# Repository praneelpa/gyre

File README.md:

<h1 align="center">
  <br>
  
  <br>
  Gyre V1
  <br>
</h1>

<h4 align="center">
  An ESP32-S3 development board with a live 3D orientation view and voice control for LED strips!
</h4>

> **🚧 Work in progress:** Gyre is in the design stage. The PCB routing has been completed, but nothing has been built or tested yet.

## Features

- **ESP32-S3-MINI-1** module with WiFi, Bluetooth and native USB
- **Live 3D view** - a 6-axis IMU drives a web page that rotates a 3D model of the board in real time, over USB
- **Voice control** - an I2S microphone (ICS-43434) and a small on-device model that listens for commands and controls an external NeoPixel LED strip
- **Raspberry Pi Pico form factor** (21 x 51 mm) with Pico-style 2.54 mm pin headers
- **Still a normal ESP32** - every usable GPIO goes to the headers, so blinking an LED or flashing your own firmware works as usual. Anything onboard that uses a pin has a solder jumper, so you can free the pin
- **USB-C** for power, programming and data
- **BOOT and RESET buttons**
- **Three status LEDs** - PWR, USR (for your own code) and ACT (blinks on activity)
- **4-layer PCB** with a black solder mask and gold (ENIG) pads

## Functionality

### Live 3D view

1. The IMU measures the board's motion.
2. The ESP32 combines the readings into an orientation and sends it over USB serial.
3. A web page in Chrome or Edge reads the serial port (Web Serial) and rotates a 3D model of the board to match.

There's no driver or app to install. The IMU has no compass, so left-right turning (yaw) will slowly drift. That's a known limit of this kind of sensor.

### Voice control

1. The microphone sends audio to the ESP32 over I2S.
2. A small model running on the ESP32 listens for trained words such as "on", "off", colors and brightness levels.
3. Recognized words are combined into a command, for example "blue lights".
4. The ESP32 sends the command to the LED strip through a level shifter on the data line.

The strip is a separate part and has its own 5 V supply. Gyre only sends the data signal, because a room-sized strip can draw far more current than USB provides. The model is trained on a fixed set of words, so it works best for the voice it was trained on.

## PCB

Designed in KiCad. The board uses a 4-layer stackup (SIG/GND/PWR/SIG) with a black solder mask, gold (ENIG) pads and white silkscreen.

### Schematic

### PCB Layers

**Layer 1 (F.Cu):**

**Layer 2 (Ground):**

**Layer 3 (+3.3V):**

**Layer 4 (B.Cu):**

**Front View:**

**Back View:**

### BOM
| Designator            | Footprint                         | Qty Per Board | Order Qty | Value              | Price   | LCSC Part Number | LCSC Part Link                                     |
|-----------------------|-----------------------------------|---------------|-----------|--------------------|---------|------------------|----------------------------------------------------|
| C1                    | 0805                              | 1             | 20        | 10u                | $0.4220 | C1713            | https://www.lcsc.com/product-detail/C1713.html     |
| C10, C11, C12, C4, C7 | 0805                              | 5             | 20        | 0.1u               | $0.2780 | C49678           | https://www.lcsc.com/product-detail/C49678.html    |
| C3                    | 0805                              | 1             | 20        | 1u                 | $0.5240 | C24123           | https://www.lcsc.com/product-detail/C24123.html    |
| C5                    | 0805                              | 1             | 10        | 22u                | $0.2190 | C29277           | https://www.lcsc.com/product-detail/C29277.html    |
| C8                    | 0805                              | 1             | 100       | 10n                | $0.6600 | C282728          | https://www.lcsc.com/product-detail/C282728.html   |
| C9                    | 0805                              | 1             | 20        | 2.2u               | $0.9680 | C1731            | https://www.lcsc.com/product-detail/C1731.html     |
| D1                    | SOT-23-6_L2.9-W1.6-P0.95-LS2.8-BL | 1             | 5         | USBLC6-2SC6        | $0.7680 | C7519            | https://www.lcsc.com/product-detail/C7519.html     |
| D2                    | 0805                              | 1             | 50        | ACT red            | $0.6300 | C84256           | https://www.lcsc.com/product-detail/C84256.html    |
| D3                    | 0805                              | 1             | 100       | USR blue           | $0.5900 | C7496833         | https://www.lcsc.com/product-detail/C7496833.html  |
| D4                    | 0805                              | 1             | 50        | VOICE white        | $0.4150 | C55072219        | https://www.lcsc.com/product-detail/C55072219.html |
| J1, J2, J3, J4        | PinHeaders_1x40_P2.54mm_Vertical  | 2             | 5         | Conn_01x40         | $0.8160 | C2337            | https://www.lcsc.com/product-detail/C2337.html     |
| R1, R2                | 0805                              | 2             | 100       | 5.1K               | $0.2900 | C27834           | https://www.lcsc.com/product-detail/C27834.html    |
| R10, R11              | 0805                              | 2             | 100       | 100                | $0.3500 | C105577          | https://www.lcsc.com/product-detail/C105577.html   |
| R3, R6, R8            | 0805                              | 3             | 100       | 10k                | $0.3200 | C17414           | https://www.lcsc.com/product-detail/C17414.html    |
| R4                    | 0805                              | 1             | 100       | 499                | $0.2300 | C2933453         | https://www.lcsc.com/product-detail/C2933453.html  |
| R5                    | 0805                              | 1             | 100       | 100k               | $0.3600 | C149504          | https://www.lcsc.com/product-detail/C149504.html   |
| R7, R9                | 0805                              | 2             | 100       | 330                | $0.2500 | C2930157         | https://www.lcsc.com/product-detail/C2930157.html  |
| SW1                   | SW-SMD_L3.9-W2.9-LS4.8            | 1             | 5         | BOOT               | $0.4295 | C596279          | https://www.lcsc.com/product-detail/C596279.html   |
| SW2                   | SW-SMD_L3.9-W2.9-LS4.8            | 1             | 5         | RESET              | $0.4295 | C596279          | https://www.lcsc.com/product-detail/C596279.html   |
| U1                    | SOT-25-5_L2.9-W1.6-P0.95-LS2.8-BL | 1             | 5         | AP2112K-3.3TRG1    | $0.8415 | C51118           | https://www.lcsc.com/product-detail/C51118.html    |
| U2                    | BULETM-SMD_ESP32-S3-MINI-1-N8     | 1             | 1         | ESP32-S3-MINI-1-N8 | $4.7617 | C2913206         | https://www.lcsc.com/product-detail/C2913206.html  |
| U3                    | LGA-14_L3.0-W2.5-P0.50-TL         | 1             | 2         | ICM-42688-P        | $3.6600 | C54308212        | https://www.lcsc.com/product-detail/C54308212.html |
| U4                    | MIC-SMD_6P-L3.5-W2.7-P0.90-BL     | 1             | 1         | ICS-43434_C5656610 | $4.2908 | C5656610         | https://www.lcsc.com/product-detail/C5656610.html  |
| U5                    | SOT-25-5_L2.9-W1.6-P0.95-LS2.8-BL | 1             | 1         | 74AHCT1G125GV      | $0.0734 | C52140417        | https://www.lcsc.com/product-detail/C52140417.html |
| USB1                  | USB-C-SMD_TYPE-C-16PIN-2MD-073    | 1             | 20        | TYPE-C 16PIN 2MD   | $1.3900 | C2765186         | https://www.lcsc.com/product-detail/C2765186.html  |

## Credits

This project uses:

- [KiCad](https://www.kicad.org/)
- [Espressif](https://www.espressif.com/) for the ESP32-S3 module and its hardware design guidelines

---

> GitHub [@praneelpa](https://github.com/praneelpa) ·
> MIT License

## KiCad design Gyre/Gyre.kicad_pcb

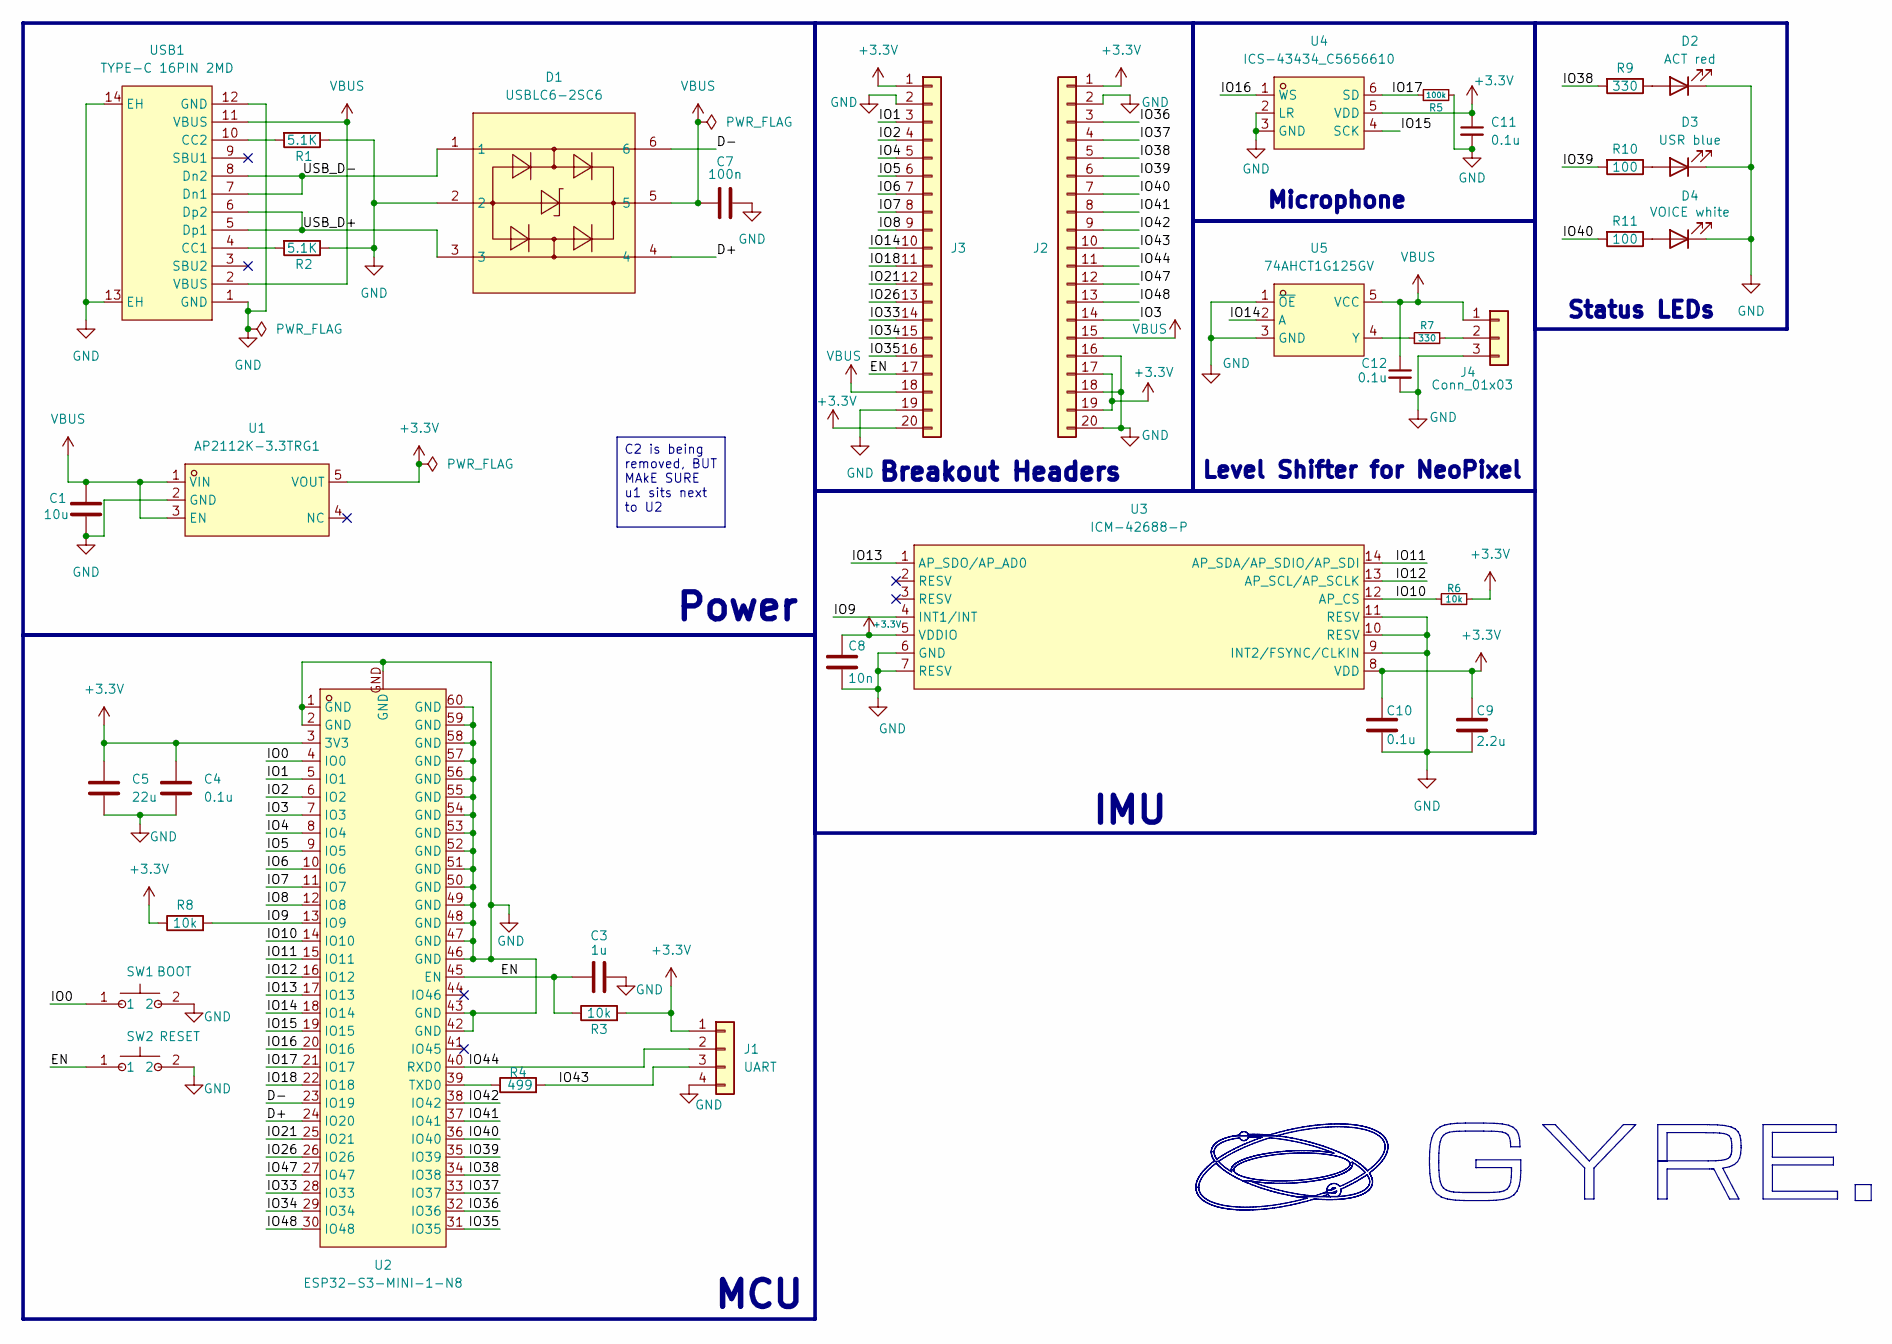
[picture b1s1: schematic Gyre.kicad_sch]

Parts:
C1: 10u; C_0805_2012Metric_Pad1.18x1.45mm_HandSolder
C3: 1u; C_0805_2012Metric_Pad1.18x1.45mm_HandSolder
C4, C10, C11, C12: 0.1u; C_0805_2012Metric_Pad1.18x1.45mm_HandSolder
C5: 22u; C_0805_2012Metric_Pad1.18x1.45mm_HandSolder
C7: 100n; C_0805_2012Metric_Pad1.18x1.45mm_HandSolder
C8: 10n; C_0805_2012Metric_Pad1.18x1.45mm_HandSolder
C9: 2.2u; C_0805_2012Metric_Pad1.18x1.45mm_HandSolder
D1: USBLC6-2SC6; SOT-23-6_L2.9-W1.6-P0.95-LS2.8-BL; MPN USBLC6-2SC6; LCSC Part C7519
D2: ACT red; LED_0805_2012Metric_Pad1.15x1.40mm_HandSolder
D3: USR blue; LED_0805_2012Metric_Pad1.15x1.40mm_HandSolder
D4: VOICE white; LED_0805_2012Metric_Pad1.15x1.40mm_HandSolder
J1: UART; PinHeader_1x04_P2.54mm_Vertical
J2, J3: Conn_01x20; PinHeader_1x20_P2.54mm_Vertical
J4: Conn_01x03; PinHeader_1x03_P2.54mm_Vertical
R1, R2: 5.1K; R_0805_2012Metric_Pad1.20x1.40mm_HandSolder
R3, R6, R8: 10k; R_0805_2012Metric_Pad1.20x1.40mm_HandSolder
R4: 499; R_0805_2012Metric_Pad1.20x1.40mm_HandSolder
R5: 100k; R_0805_2012Metric_Pad1.20x1.40mm_HandSolder
R7, R9: 330; R_0805_2012Metric_Pad1.20x1.40mm_HandSolder
R10, R11: 100; R_0805_2012Metric_Pad1.20x1.40mm_HandSolder
SW1: BOOT; SW-SMD_L3.9-W2.9-LS4.8; MPN TS-1807R-2026; LCSC Part C596279
SW2: RESET; SW-SMD_L3.9-W2.9-LS4.8; MPN TS-1807R-2026; LCSC Part C596279
U1: AP2112K-3.3TRG1; SOT-25-5_L2.9-W1.6-P0.95-LS2.8-BL; MPN AP2112K-3.3TRG1; LCSC Part C51118
U2: ESP32-S3-MINI-1-N8; BULETM-SMD_ESP32-S3-MINI-1-N8; MPN ESP32-S3-MINI-1-N8; LCSC Part C2913206
U3: ICM-42688-P; LGA-14_L3.0-W2.5-P0.50-TL; MPN ICM-42688-P; LCSC Part C1850418
U4: ICS-43434_C5656610; MIC-SMD_6P-L3.5-W2.7-P0.90-BL; MPN ICS-43434; LCSC Part C5656610
U5: 74AHCT1G125GV; SOT-25-5_L2.9-W1.6-P0.95-LS2.8-BL; MPN 74AHCT1G125GV; LCSC Part C52140417
USB1: TYPE-C 16PIN 2MD; USB-C-SMD_TYPE-C-16PIN-2MD-073; MPN TYPE-C 16PIN 2MD(073); LCSC Part C2765186

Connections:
+3.3V: C4.1, C5.1, C8.1, C9.1, C10.1, C11.1, J1.1, J2.1, J2.17, J2.19, J3.1, J3.20, R3.2, R6.2, R8.1, U1.5 (VOUT), U2.3 (3V3), U3.5 (VDDIO), U3.8 (VDD), U4.5 (VDD)
/D+: D1.4, U2.24 (IO20)
/D-: D1.6, U2.23 (IO19)
/EN: C3.1, J3.17, R3.1, SW2.1, U2.45 (EN)
/IO0: SW1.1, U2.4 (IO0)
/IO1: J3.3, U2.5 (IO1)
/IO2: J3.4, U2.6 (IO2)
/IO3: J2.14, U2.7 (IO3)
/IO4: J3.5, U2.8 (IO4)
/IO5: J3.6, U2.9 (IO5)
/IO6: J3.7, U2.10 (IO6)
/IO7: J3.8, U2.11 (IO7)
/IO8: J3.9, U2.12 (IO8)
/IO9: R8.2, U2.13 (IO9), U3.4 (INT1/INT)
/IO10: R6.1, U2.14 (IO10), U3.12 (AP_CS)
/IO11: U2.15 (IO11), U3.14 (AP_SDA/AP_SDIO/AP_SDI)
/IO12: U2.16 (IO12), U3.13 (AP_SCL/AP_SCLK)
/IO13: U2.17 (IO13), U3.1 (AP_SDO/AP_AD0)
/IO14: J3.10, U2.18 (IO14), U5.2 (A)
/IO15: U2.19 (IO15), U4.4 (SCK)
/IO16: U2.20 (IO16), U4.1 (WS)
/IO17: R5.1, U2.21 (IO17), U4.6 (SD)
/IO18: J3.11, U2.22 (IO18)
/IO21: J3.12, U2.25 (IO21)
/IO26: J3.13, U2.26 (IO26)
/IO33: J3.14, U2.28 (IO33)
/IO34: J3.15, U2.29 (IO34)
/IO35: J3.16, U2.31 (IO35)
/IO36: J2.3, U2.32 (IO36)
/IO37: J2.4, U2.33 (IO37)
/IO38: J2.5, R9.2, U2.34 (IO38)
/IO39: J2.6, R10.2, U2.35 (IO39)
/IO40: J2.7, R11.2, U2.36 (IO40)
/IO41: J2.8, U2.37 (IO41)
/IO42: J2.9, U2.38 (IO42)
/IO43: J1.3, J2.10, R4.2
/IO44: J1.2, J2.11, U2.40 (RXD0)
/IO47: J2.12, U2.27 (IO47)
/IO48: J2.13, U2.30 (IO48)
/USB_D+: D1.3, USB1.5 (Dp1), USB1.6 (Dp2)
/USB_D-: D1.1, USB1.7 (Dn1), USB1.8 (Dn2)
GND: C1.2, C3.2, C4.2, C5.2, C7.2, C8.2, C9.2, C10.2, C11.2, C12.2, D1.2, D2.1 (K), D3.1 (K), D4.1 (K), J1.4, J2.2, J2.16, J2.18, J2.20, J3.2, J3.19, J4.3, R1.1, R2.1, R5.2, SW1.2, SW2.2, U1.2 (GND), U2.1 (GND), U2.2 (GND), U2.42 (GND), U2.43 (GND), U2.46 (GND), U2.47 (GND), U2.48 (GND), U2.49 (GND), U2.50 (GND), U2.51 (GND), U2.52 (GND), U2.53 (GND), U2.54 (GND), U2.55 (GND), U2.56 (GND), U2.57 (GND), U2.58 (GND), U2.59 (GND), U2.60 (GND), U2.GND, U3.6 (GND), U3.7 (RESV), U3.9 (INT2/FSYNC/CLKIN), U3.10 (RESV), U3.11 (RESV), U4.2 (LR), U4.3 (GND), U5.1 (~OE), U5.3 (GND), USB1.1 (GND), USB1.12 (GND), USB1.13 (EH), USB1.14 (EH)
unnamed: D2.2 (A), R9.1
unnamed: D3.2 (A), R10.1
unnamed: D4.2 (A), R11.1
unnamed: J4.2, R7.2
unnamed: R4.1, U2.39 (TXD0)
unnamed: R7.1, U5.4 (Y)
unnamed: R2.2, USB1.4 (CC1)
unnamed: R1.2, USB1.10 (CC2)
VBUS: C1.1, C7.1, C12.1, D1.5, J2.15, J3.18, J4.1, U1.1 (VIN), U1.3 (EN), U5.5 (VCC), USB1.2 (VBUS), USB1.11 (VBUS)

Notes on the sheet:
IMU
Status LEDs
Microphone
Level Shifter for NeoPixel
Breakout Headers
MCU
Power
C2 is being removed, BUT MAkE SURE u1 sits next to U2

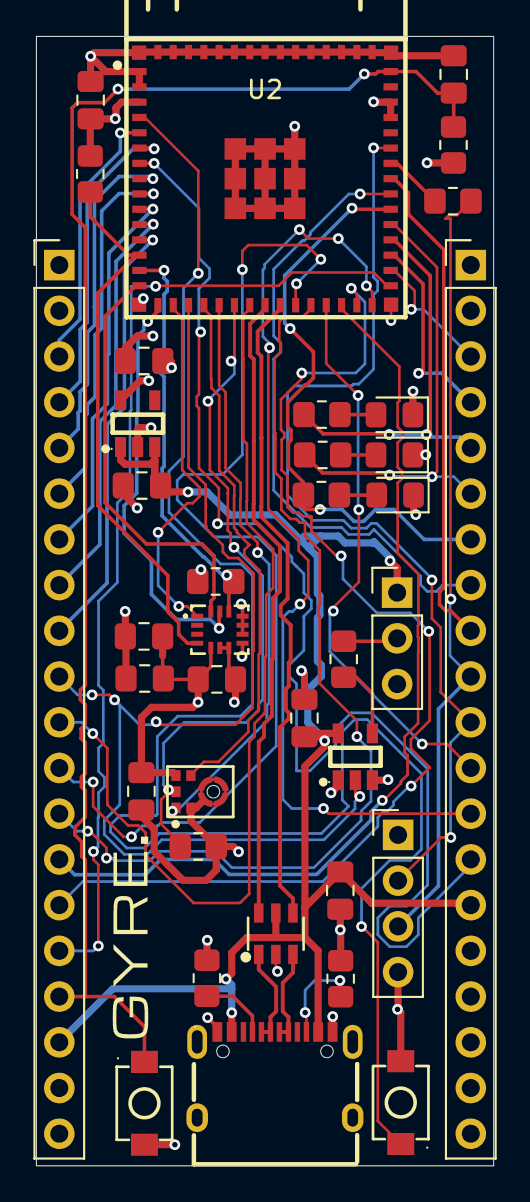
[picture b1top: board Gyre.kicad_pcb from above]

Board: 4 copper layers, 25.4 x 62.7 mm, 37 parts (0 on the bottom side), 51 nets.

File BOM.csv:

Designator,Footprint,Qty Per Board,Order Qty,Value,Price,LCSC Part Number,LCSC Part Link
C1,0805,1,20,10u,$0.4220,C1713,https://www.lcsc.com/product-detail/C1713.html
"C10, C11, C12, C4, C7",0805,5,20,0.1u,$0.2780,C49678,https://www.lcsc.com/product-detail/C49678.html
C3,0805,1,20,1u,$0.5240,C24123,https://www.lcsc.com/product-detail/C24123.html
C5,0805,1,10,22u,$0.2190,C29277,https://www.lcsc.com/product-detail/C29277.html
C8,0805,1,100,10n,$0.6600,C282728,https://www.lcsc.com/product-detail/C282728.html
C9,0805,1,20,2.2u,$0.9680,C1731,https://www.lcsc.com/product-detail/C1731.html
D1,SOT-23-6_L2.9-W1.6-P0.95-LS2.8-BL,1,5,USBLC6-2SC6,$0.7680,C7519,https://www.lcsc.com/product-detail/C7519.html
D2,0805,1,50,ACT red,$0.6300,C84256,https://www.lcsc.com/product-detail/C84256.html
D3,0805,1,100,USR blue,$0.5900,C7496833,https://www.lcsc.com/product-detail/C7496833.html
D4,0805,1,50,VOICE white,$0.4150,C55072219,https://www.lcsc.com/product-detail/C55072219.html
"J1, J2, J3, J4",PinHeaders_1x40_P2.54mm_Vertical,2,5,Conn_01x40,$0.8160,C2337,https://www.lcsc.com/product-detail/C2337.html
"R1, R2",0805,2,100,5.1K,$0.2900,C27834,https://www.lcsc.com/product-detail/C27834.html
"R10, R11",0805,2,100,100,$0.3500,C105577,https://www.lcsc.com/product-detail/C105577.html
"R3, R6, R8",0805,3,100,10k,$0.3200,C17414,https://www.lcsc.com/product-detail/C17414.html
R4,0805,1,100,499,$0.2300,C2933453,https://www.lcsc.com/product-detail/C2933453.html
R5,0805,1,100,100k,$0.3600,C149504,https://www.lcsc.com/product-detail/C149504.html
"R7, R9",0805,2,100,330,$0.2500,C2930157,https://www.lcsc.com/product-detail/C2930157.html
SW1,SW-SMD_L3.9-W2.9-LS4.8,1,5,BOOT,$0.4295,C596279,https://www.lcsc.com/product-detail/C596279.html
SW2,SW-SMD_L3.9-W2.9-LS4.8,1,5,RESET,$0.4295,C596279,https://www.lcsc.com/product-detail/C596279.html
U1,SOT-25-5_L2.9-W1.6-P0.95-LS2.8-BL,1,5,AP2112K-3.3TRG1,$0.8415,C51118,https://www.lcsc.com/product-detail/C51118.html
U2,BULETM-SMD_ESP32-S3-MINI-1-N8,1,1,ESP32-S3-MINI-1-N8,$4.7617,C2913206,https://www.lcsc.com/product-detail/C2913206.html
U3,LGA-14_L3.0-W2.5-P0.50-TL,1,2,ICM-42688-P,$3.6600,C54308212,https://www.lcsc.com/product-detail/C54308212.html
U4,MIC-SMD_6P-L3.5-W2.7-P0.90-BL,1,1,ICS-43434_C5656610,$4.2908,C5656610,https://www.lcsc.com/product-detail/C5656610.html
U5,SOT-25-5_L2.9-W1.6-P0.95-LS2.8-BL,1,1,74AHCT1G125GV,$0.0734,C52140417,https://www.lcsc.com/product-detail/C52140417.html
USB1,USB-C-SMD_TYPE-C-16PIN-2MD-073,1,20,TYPE-C 16PIN 2MD,$1.3900,C2765186,https://www.lcsc.com/product-detail/C2765186.html
